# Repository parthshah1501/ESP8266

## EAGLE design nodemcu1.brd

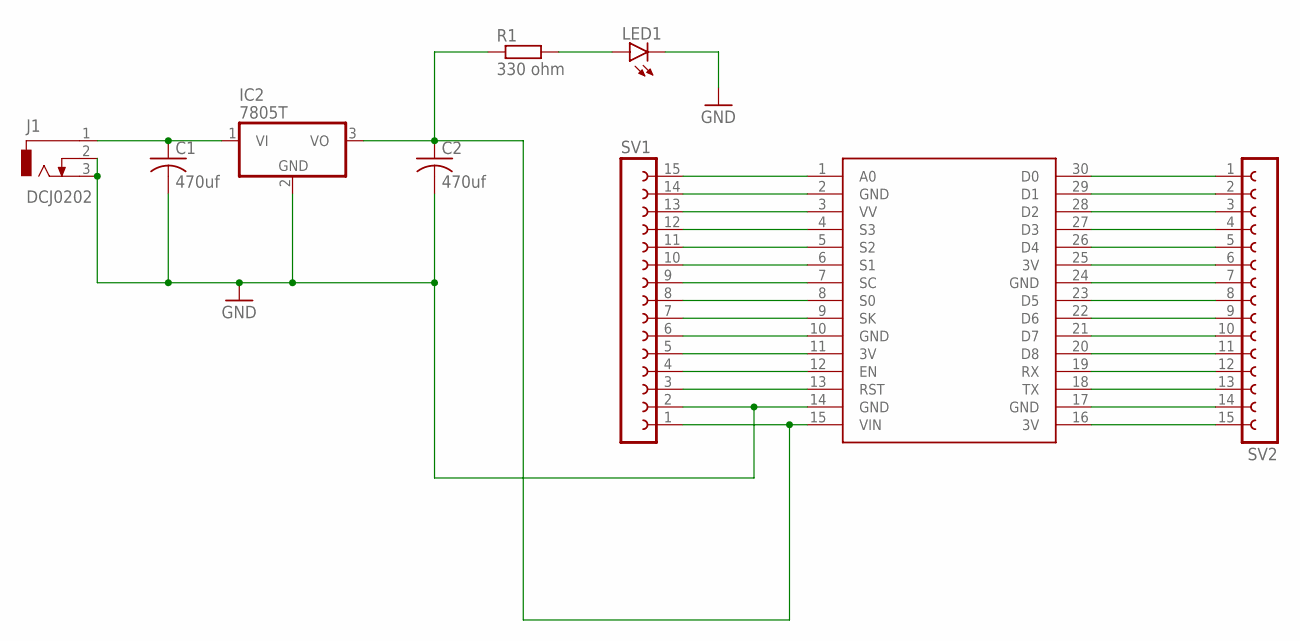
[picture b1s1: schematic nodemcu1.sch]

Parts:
C1, C2: 470uf; C025-024X044
IC2: 7805T; TO220H
J1: DCJ0202
LED1: LEDLD260; LD260
R1: 330 ohm; 0204/5
SV1, SV2: FE15-1; FE15
U$1: NODEMCU

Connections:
GND: C1.2, C2.2, IC2.2 (GND), J1.2, J1.3, LED1.K (C), SV1.2, U$1.14 (GND)
unnamed: SV1.3, U$1.13 (RST)
unnamed: SV1.4, U$1.12 (EN)
unnamed: SV1.5, U$1.11 (3V)
unnamed: SV1.6, U$1.10 (GND)
unnamed: SV1.7, U$1.9 (SK)
unnamed: SV1.8, U$1.8 (S0)
unnamed: SV1.9, U$1.7 (SC)
unnamed: SV1.10, U$1.6 (S1)
unnamed: SV1.11, U$1.5 (S2)
unnamed: SV1.12, U$1.4 (S3)
unnamed: SV1.13, U$1.3 (VV)
unnamed: SV1.14, U$1.2 (GND)
unnamed: SV1.15, U$1.1 (A0)
unnamed: SV2.1, U$1.30 (D0)
unnamed: SV2.2, U$1.29 (D1)
unnamed: SV2.3, U$1.28 (D2)
unnamed: SV2.4, U$1.27 (D3)
unnamed: SV2.5, U$1.26 (D4)
unnamed: SV2.6, U$1.25 (3V)
unnamed: SV2.7, U$1.24 (GND)
unnamed: SV2.8, U$1.23 (D5)
unnamed: SV2.9, U$1.22 (D6)
unnamed: SV2.10, U$1.21 (D7)
unnamed: SV2.11, U$1.20 (D8)
unnamed: SV2.12, U$1.19 (RX)
unnamed: SV2.13, U$1.18 (TX)
unnamed: SV2.14, U$1.17 (GND)
unnamed: SV2.15, U$1.16 (3V)
unnamed: C2.1, IC2.3 (VO), R1.1, SV1.1, U$1.15 (VIN)
unnamed: C1.1, IC2.1 (VI), J1.1
unnamed: LED1.A, R1.2

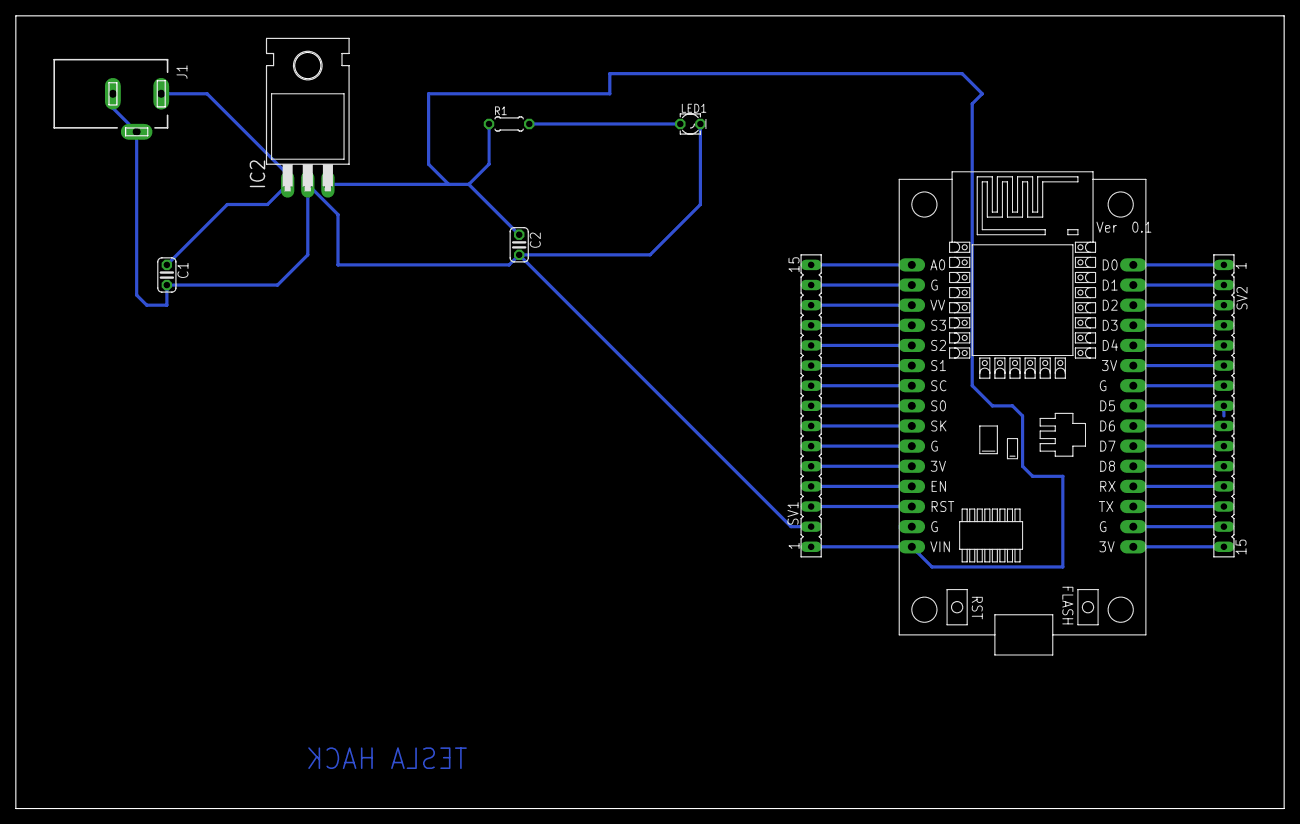
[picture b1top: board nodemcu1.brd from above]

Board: 2 copper layers, 160.0 x 100.0 mm, 9 parts (0 on the bottom side), 32 nets.
